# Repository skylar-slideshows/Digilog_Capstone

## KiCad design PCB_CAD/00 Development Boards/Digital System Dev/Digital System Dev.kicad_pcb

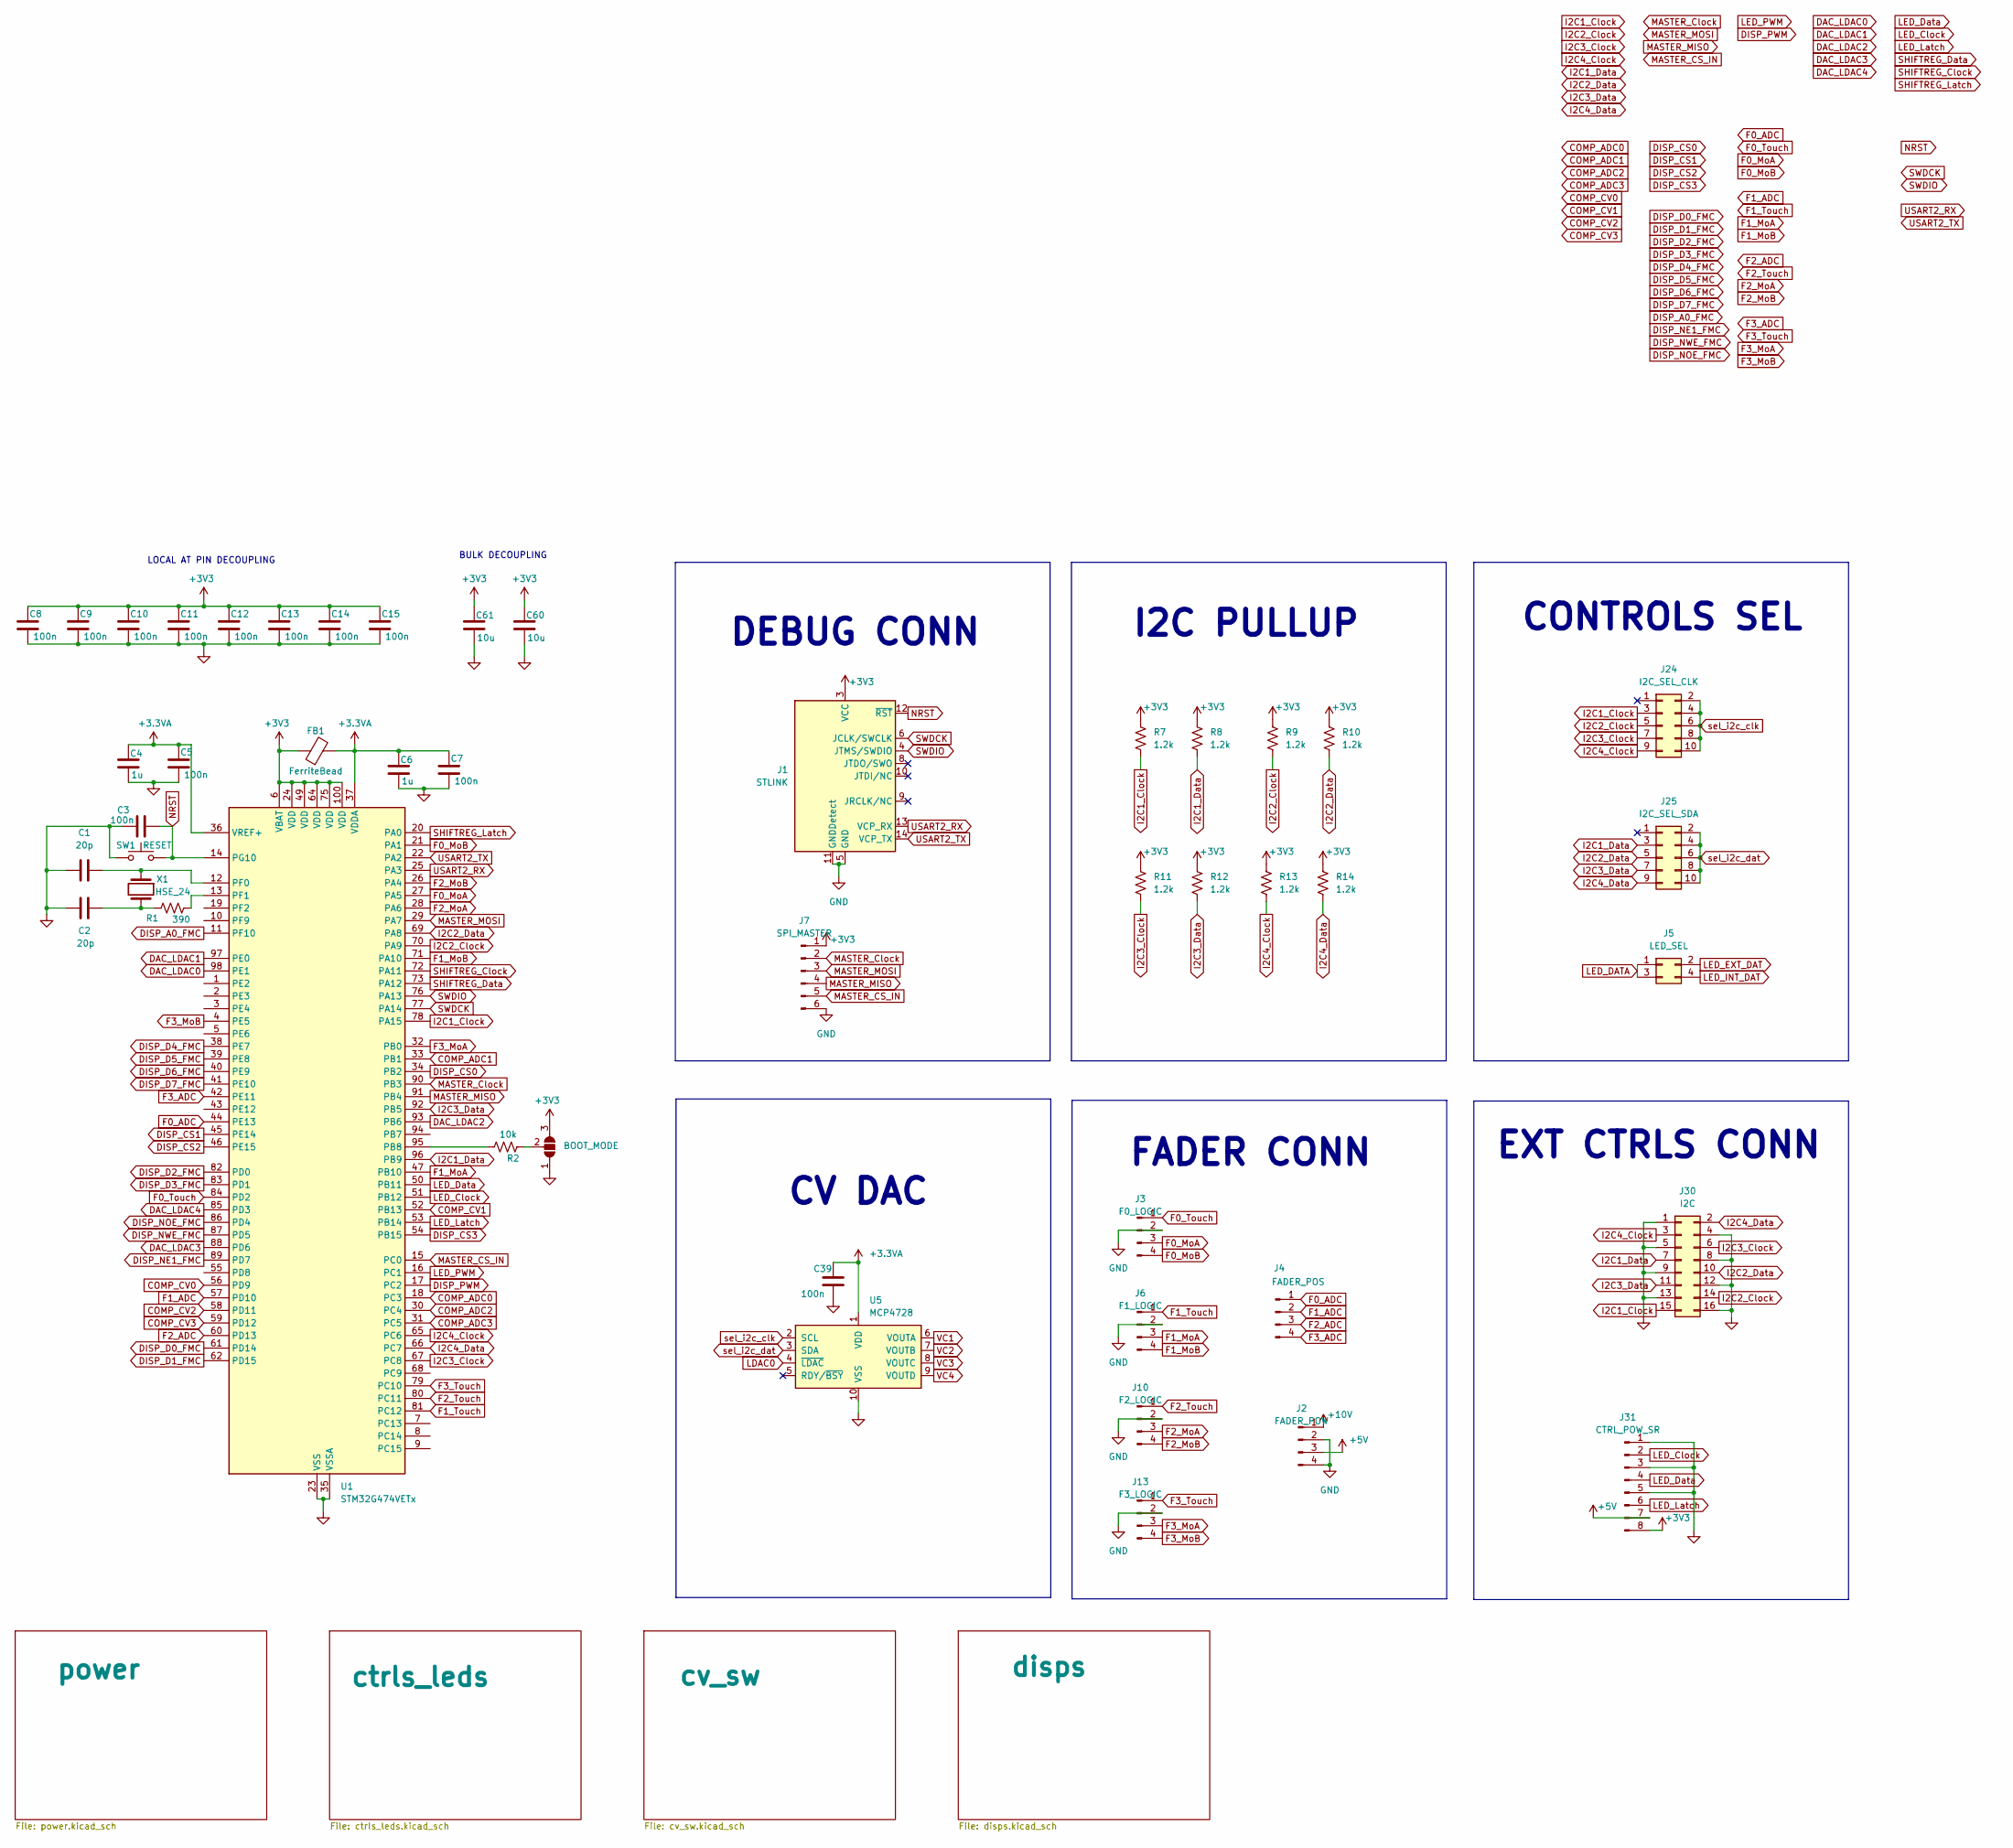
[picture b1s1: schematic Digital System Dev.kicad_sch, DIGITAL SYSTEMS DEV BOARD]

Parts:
C1, C2: 20p; C_0603_1608Metric; LCSC C1648
C3, C5, C7, C8, C9, C10, C11, C12, C13, C14, C15, C39: 100n; C_0603_1608Metric; LCSC C1590
C4, C6: 1u; C_0603_1608Metric; LCSC C1592
C60, C61: 10u; C_1206_3216Metric; LCSC C1849
FB1: FerriteBead; Ferrite_0603_1608Metric; LCSC C1002
J1: STLINK; FTSH-107-01-L-DV-K-TR; LCSC C5307809
J2: FADER_POW; PinHeader_1x04_P2.54mm_Vertical
J3: F0_LOGIC; PinHeader_1x04_P2.54mm_Vertical
J4: FADER_POS; PinHeader_1x04_P2.54mm_Vertical
J5: LED_SEL; PinHeader_2x02_P2.54mm_Vertical
J6: F1_LOGIC; PinHeader_1x04_P2.54mm_Vertical
J7: SPI_MASTER; PinHeader_1x06_P2.54mm_Vertical
J10: F2_LOGIC; PinHeader_1x04_P2.54mm_Vertical
J13: F3_LOGIC; PinHeader_1x04_P2.54mm_Vertical
J24: I2C_SEL_CLK; PinHeader_2x05_P2.54mm_Vertical
J25: I2C_SEL_SDA; PinHeader_2x05_P2.54mm_Vertical
J30: I2C; PinHeader_2x08_P1.27mm_Vertical
J31: CTRL_POW_SR; PinHeader_1x08_P2.54mm_Vertical
R1: 390; R_1206_3216Metric; LCSC C497314
R2: 10k
R7, R8, R9, R10, R11, R12, R13, R14: 1.2k
SP1: BOOT_MODE; SolderJumper-3_P2.0mm_Open_TrianglePad1.0x1.5mm
SW1: RESET; SW_Push_1P1T_NO_CK_KMR2; LCSC C72443
U1: STM32G474VETx; LQFP-100_14x14mm_P0.5mm; LCSC C2970837
U5: MCP4728; MSOP-10_3x3mm_P0.5mm; LCSC C478093
X1: HSE_24; Crystal_SMD_HC49-SD; LCSC C117881

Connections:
+3.3VA: C4.1, C5.1, C6.1, C7.1, C39.1, FB1.2, U1.36 (VREF+), U1.37 (VDDA), U5.1 (VDD)
+3V3: C8.1, C9.1, C10.1, C11.1, C12.1, C13.1, C14.1, C15.1, C60.1, C61.1, FB1.1, J1.3 (VCC), J7.1, J31.8, R7.1, R8.1, R9.1, R10.1, R11.1, R12.1, R13.1, R14.1, SP1.3 (B), U1.6 (VBAT), U1.24 (VDD), U1.49 (VDD), U1.64 (VDD), U1.75 (VDD), U1.100 (VDD); also elsewhere on the board
+5V: J2.3, J31.7; also elsewhere on the board
+10V: J2.1; also elsewhere on the board
COMP_ADC0: U1.18 (PC3)
COMP_ADC1: U1.33 (PB1)
COMP_ADC2: U1.30 (PC4)
COMP_ADC3: U1.31 (PC5)
COMP_CV0: U1.56 (PD9)
COMP_CV1: U1.52 (PB13)
COMP_CV2: U1.58 (PD11)
COMP_CV3: U1.59 (PD12)
DAC_LDAC0: U1.98 (PE1)
DAC_LDAC1: U1.97 (PE0)
DAC_LDAC2: U1.93 (PB6)
DAC_LDAC3: U1.88 (PD6)
DAC_LDAC4: U1.85 (PD3)
DISP_A0_FMC: U1.11 (PF10)
DISP_CS0: U1.34 (PB2)
DISP_CS1: U1.45 (PE14)
DISP_CS2: U1.46 (PE15)
DISP_CS3: U1.54 (PB15)
DISP_D0_FMC: U1.61 (PD14)
DISP_D1_FMC: U1.62 (PD15)
DISP_D2_FMC: U1.82 (PD0)
DISP_D3_FMC: U1.83 (PD1)
DISP_D4_FMC: U1.38 (PE7)
DISP_D5_FMC: U1.39 (PE8)
DISP_D6_FMC: U1.40 (PE9)
DISP_D7_FMC: U1.41 (PE10)
DISP_NE1_FMC: U1.89 (PD7)
DISP_NOE_FMC: U1.86 (PD4)
DISP_NWE_FMC: U1.87 (PD5)
DISP_PWM: U1.17 (PC2); also elsewhere on the board
F0_ADC: J4.1, U1.44 (PE13)
F0_MoA: J3.3, U1.27 (PA5)
F0_MoB: J3.4, U1.21 (PA1)
F0_Touch: J3.1, U1.84 (PD2)
F1_ADC: J4.2, U1.57 (PD10)
F1_MoA: J6.3, U1.47 (PB10)
F1_MoB: J6.4, U1.71 (PA10)
F1_Touch: J6.1, U1.81 (PC12)
F2_ADC: J4.3, U1.60 (PD13)
F2_MoA: J10.3, U1.28 (PA6)
F2_MoB: J10.4, U1.26 (PA4)
F2_Touch: J10.1, U1.80 (PC11)
F3_ADC: J4.4, U1.42 (PE11)
F3_MoA: J13.3, U1.32 (PB0)
F3_MoB: J13.4, U1.4 (PE5)
F3_Touch: J13.1, U1.79 (PC10)
I2C1_Clock: J24.3, J30.15, R7.2, U1.78 (PA15)
I2C1_Data: J25.3, J30.7, R8.2, U1.96 (PB9)
I2C2_Clock: J24.5, J30.14, R9.2, U1.70 (PA9)
I2C2_Data: J25.5, J30.10, R10.2, U1.69 (PA8)
I2C3_Clock: J24.7, J30.6, R11.2, U1.67 (PC8)
I2C3_Data: J25.7, J30.11, R12.2, U1.92 (PB5)
I2C4_Clock: J24.9, J30.3, R13.2, U1.65 (PC6)
I2C4_Data: J25.9, J30.2, R14.2, U1.66 (PC7)
LDAC0: U5.4 (~LDAC)
LED_Clock: J31.2, U1.51 (PB12); also elsewhere on the board
LED_DATA: J5.1, J5.3
LED_Data: J31.4, U1.50 (PB11)
LED_EXT_DAT: J5.2
LED_INT_DAT: J5.4; also elsewhere on the board
LED_Latch: J31.6, U1.53 (PB14); also elsewhere on the board
LED_PWM: U1.16 (PC1); also elsewhere on the board
MASTER_CS_IN: J7.5, U1.15 (PC0)
MASTER_Clock: J7.2, U1.90 (PB3)
MASTER_MISO: J7.4, U1.91 (PB4)
MASTER_MOSI: J7.3, U1.29 (PA7)
NRST: C3.2, J1.12 (~RST), SW1.2, U1.14 (PG10)
unnamed: C2.2, R1.1, X1.2
unnamed: R2.2, SP1.2 (C)
unnamed: R2.1, U1.95 (PB8)
unnamed: C1.1, U1.12 (PF0), X1.1
unnamed: R1.2, U1.13 (PF1)
SHIFTREG_Clock: U1.72 (PA11); also elsewhere on the board
SHIFTREG_Data: U1.73 (PA12); also elsewhere on the board
SHIFTREG_Latch: U1.20 (PA0); also elsewhere on the board
SWDCK: J1.6 (JCLK/SWCLK), U1.77 (PA14)
SWDIO: J1.4 (JTMS/SWDIO), U1.76 (PA13)
USART2_RX: J1.13 (VCP_RX), U1.25 (PA3)
USART2_TX: J1.14 (VCP_TX), U1.22 (PA2)
VC1: U5.6 (VOUTA)
VC2: U5.7 (VOUTB)
VC3: U5.8 (VOUTC)
VC4: U5.9 (VOUTD)
sel_i2c_clk: J24.2, J24.4, J24.6, J24.8, J24.10, U5.2 (SCL); also elsewhere on the board
sel_i2c_dat: J25.2, J25.4, J25.6, J25.8, J25.10, U5.3 (SDA); also elsewhere on the board

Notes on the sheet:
I2C PULLUP
BULK DECOUPLING
DEBUG CONN
CONTROLS SEL
LOCAL AT PIN DECOUPLING
EXT CTRLS CONN
FADER CONN
CV DAC

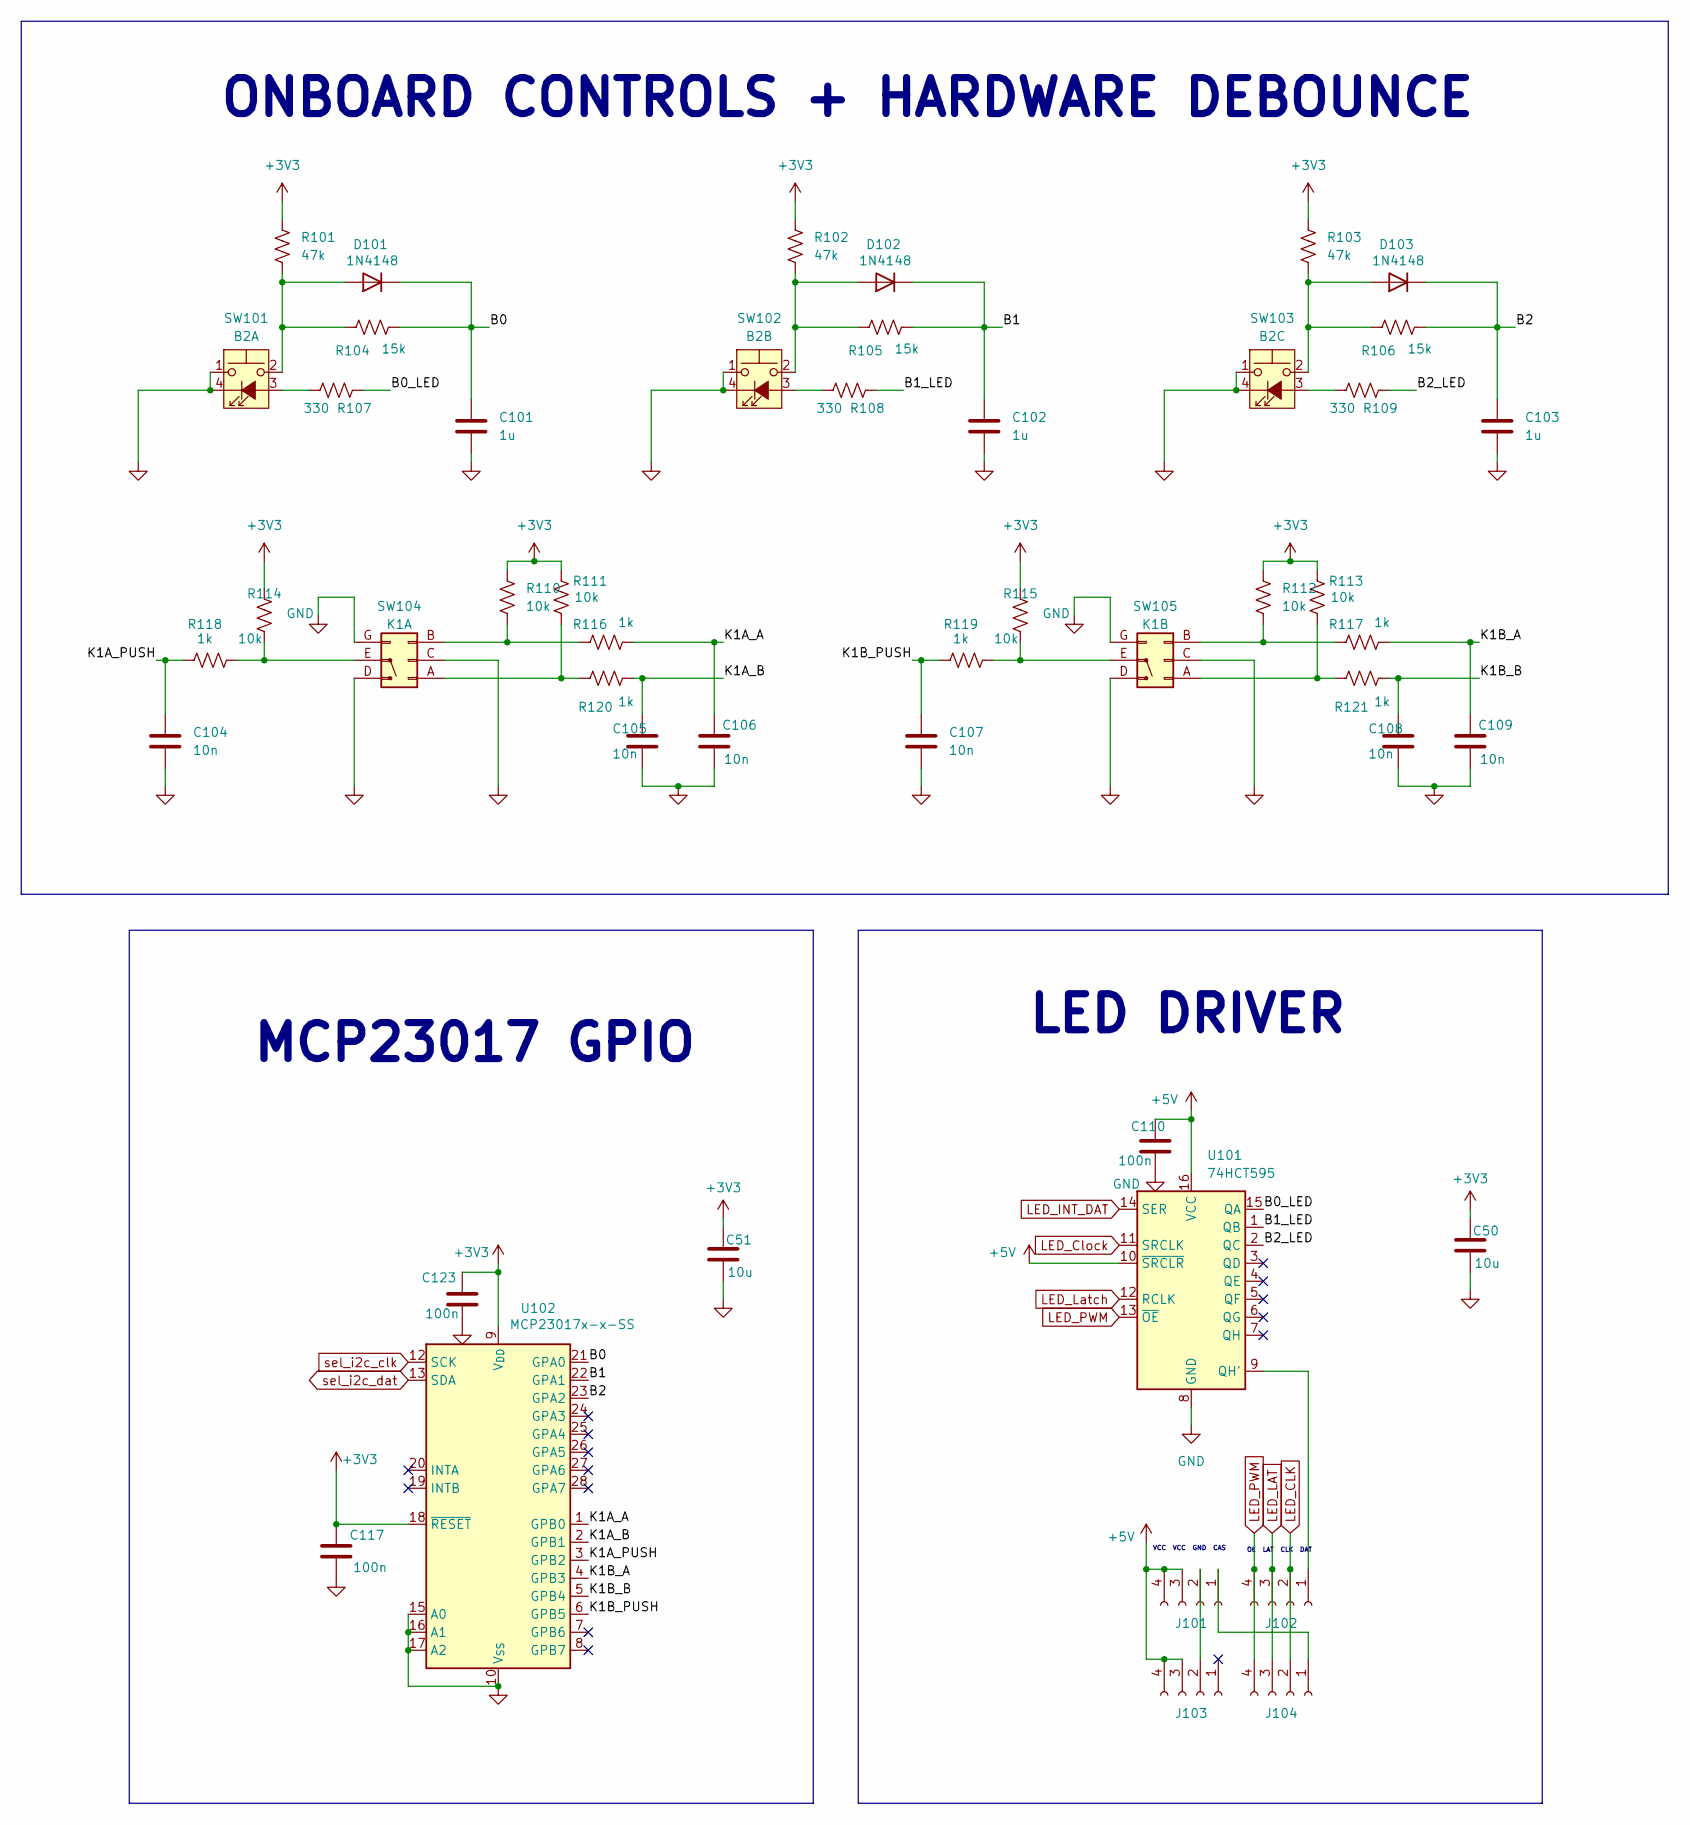
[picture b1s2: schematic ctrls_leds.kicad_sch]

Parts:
C50, C51: 10u; C_1206_3216Metric; LCSC C1849
C101, C102, C103: 1u; C_0603_1608Metric; LCSC C15849
C104, C105, C106, C107, C108, C109: 10n; C_0603_1608Metric; LCSC C57112
C110, C117, C123: 100n; C_0603_1608Metric; LCSC C1590
D101, D102, D103: 1N4148; D_SOD-323; LCSC C2128
J101, J102, J103, J104: Conn_01x04_Socket; PinSocket_1x04_P2.54mm_Vertical
R101, R102, R103: 47k; R_0603_1608Metric; LCSC C25819
R104, R105, R106: 15k; R_0603_1608Metric; LCSC C22809
R107, R108, R109: 330; R_0603_1608Metric; LCSC C23138
R110, R111, R112, R113, R114, R115: 10k; R_0603_1608Metric; LCSC C25804
R116, R117, R118, R119, R120, R121: 1k; R_0603_1608Metric; LCSC C21190
SW101: B2A; CFPB-1CC-4W6
SW102: B2B; CFPB-1CC-4W6
SW103: B2C; CFPB-1CC-4W6
SW104: K1A; EC11J0924411
SW105: K1B; EC11J0924411
U101: 74HCT595; SOIC-16_3.9x9.9mm_P1.27mm; LCSC C282339
U102: MCP23017x-x-SS; SSOP-28_5.3x10.2mm_P0.65mm

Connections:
+3V3: C50.1, C51.1, C117.1, C123.1, R101.1, R102.1, R103.1, R110.1, R111.1, R112.1, R113.1, R114.1, R115.1, U102.9 (V_{DD}), U102.18 (~RESET); also elsewhere on the board
+5V: C110.1, J101.3, J101.4, J103.3, J103.4, U101.10 (~SRCLR), U101.16 (VCC); also elsewhere on the board
/ctrls_leds/B0: C101.1, D101.1 (K), R104.2, U102.21 (GPA0)
/ctrls_leds/B0_LED: R107.2, U101.15 (QA)
/ctrls_leds/B1: C102.1, D102.1 (K), R105.2, U102.22 (GPA1)
/ctrls_leds/B1_LED: R108.2, U101.1 (QB)
/ctrls_leds/B2: C103.1, D103.1 (K), R106.2, U102.23 (GPA2)
/ctrls_leds/B2_LED: R109.2, U101.2 (QC)
/ctrls_leds/K1A_A: C106.1, R116.2, U102.1 (GPB0)
/ctrls_leds/K1A_B: C105.1, R120.2, U102.2 (GPB1)
/ctrls_leds/K1A_PUSH: C104.1, R118.1, U102.3 (GPB2)
/ctrls_leds/K1B_A: C109.1, R117.2, U102.4 (GPB3)
/ctrls_leds/K1B_B: C108.1, R121.2, U102.5 (GPB4)
/ctrls_leds/K1B_PUSH: C107.1, R119.1, U102.6 (GPB5)
LED_CLK: J102.2, J104.2
LED_Clock: U101.11 (SRCLK); also elsewhere on the board
LED_INT_DAT: U101.14 (SER); also elsewhere on the board
LED_LAT: J102.3, J104.3
LED_Latch: U101.12 (RCLK); also elsewhere on the board
LED_PWM: J102.4, J104.4, U101.13 (~OE); also elsewhere on the board
unnamed: D101.2 (A), R101.2, R104.1, SW101.2
unnamed: D102.2 (A), R102.2, R105.1, SW102.2
unnamed: D103.2 (A), R103.2, R106.1, SW103.2
unnamed: J101.1, J104.1
unnamed: J101.2, J103.2
unnamed: J102.1, U101.9 (QH')
unnamed: R107.1, SW101.3 (A)
unnamed: R108.1, SW102.3 (A)
unnamed: R109.1, SW103.3 (A)
unnamed: R111.2, R120.1, SW104.A (Pin_1)
unnamed: R110.2, R116.1, SW104.B (Pin_3)
unnamed: R114.2, R118.2, SW104.E (Pin_5)
unnamed: R113.2, R121.1, SW105.A (Pin_1)
unnamed: R112.2, R117.1, SW105.B (Pin_3)
unnamed: R115.2, R119.2, SW105.E (Pin_5)
sel_i2c_clk: U102.12 (SCK); also elsewhere on the board
sel_i2c_dat: U102.13 (SDA); also elsewhere on the board

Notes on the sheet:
OE LAT CLK DAT
MCP23017 GPIO
VCC VCC GND CAS
LED DRIVER
ONBOARD CONTROLS + HARDWARE DEBOUNCE

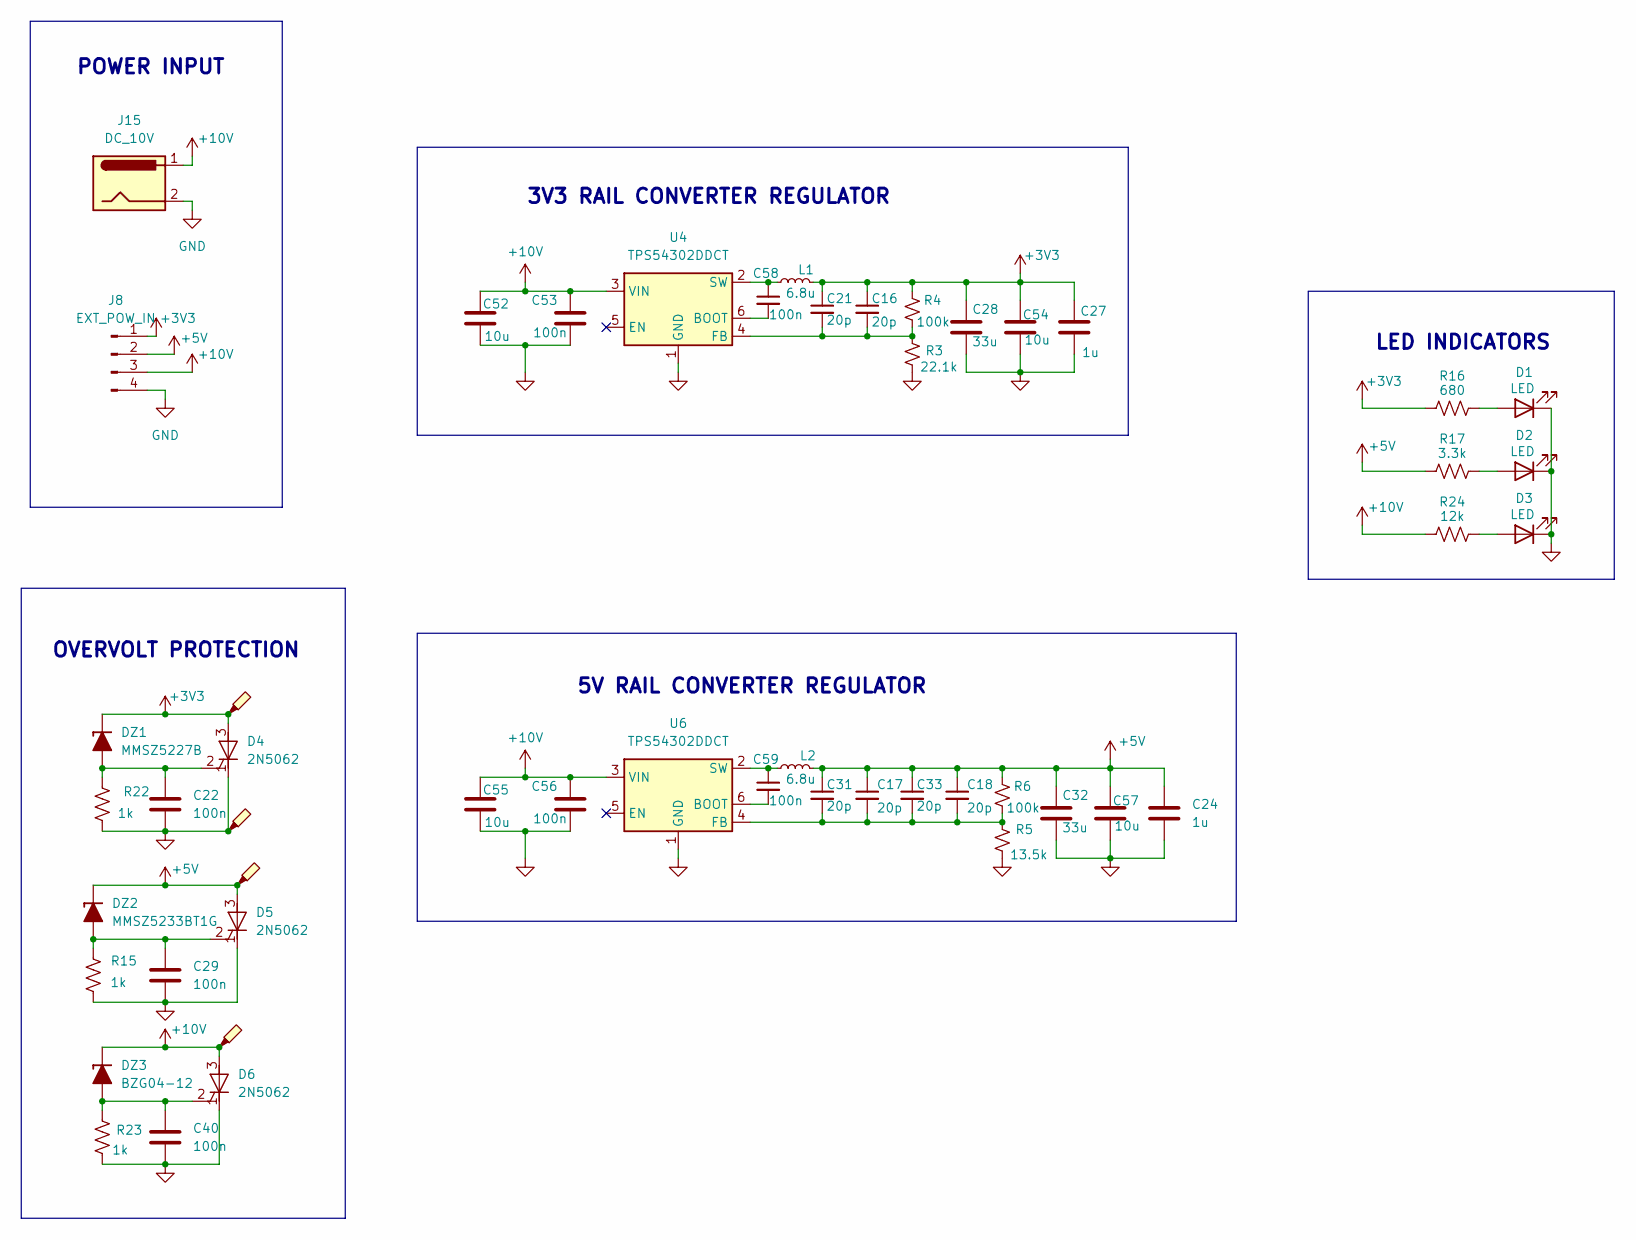
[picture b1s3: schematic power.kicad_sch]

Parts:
C16, C17, C18, C21, C31, C33: 20p; C_0603_1608Metric; LCSC C1648
C22, C29, C40, C53, C56, C58, C59: 100n; C_0603_1608Metric; LCSC C1590
C24, C27: 1u; C_0603_1608Metric; LCSC C15849
C28, C32: 33u; CP_Elec_6.3x5.4; LCSC C970684
C52, C54, C55, C57: 10u; C_1206_3216Metric; LCSC C1849
D1, D2, D3: LED; LED_0603_1608Metric; LCSC C12065
D4, D5, D6: 2N5062; TO-92
DZ1: MMSZ5227B; D_SOD-123; LCSC C707159
DZ2: MMSZ5233BT1G; D_SOD-123; LCSC C145506
DZ3: BZG04-12; D_DO-214AC_SMA; LCSC C5185905
J8: EXT_POW_IN; PinHeader_1x04_P2.54mm_Vertical
J15: DC_10V; BarrelJack_Horizontal
L1, L2: 6.8u; L_1210_3225Metric; LCSC C3040386
R3: 22.1k; R_0805_2012Metric; LCSC C17552
R4, R6: 100k
R5: 13.5k; R_0603_1608Metric; LCSC C861118
R15, R22, R23: 1k; R_0603_1608Metric; LCSC C21190
R16: 680; R_0603_1608Metric; LCSC C25822
R17: 3.3k; R_0603_1608Metric; LCSC C22978
R24: 12k; R_0603_1608Metric; LCSC C22790
TP9, TP10, TP11, TP19: TestPoint_Probe; TestPoint_Keystone_5019_Miniature
U4, U6: TPS54302DDCT; SOT-23-6; LCSC C129370

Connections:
+3V3: C16.1, C21.1, C27.1, C28.1, C54.1, D4.3 (A), DZ1.1 (K), J8.1, L1.2, R4.1, R16.1, TP9.1 (1_1); also elsewhere on the board
+5V: C17.1, C18.1, C24.1, C31.1, C32.1, C33.1, C57.1, D5.3 (A), DZ2.1 (K), J8.2, L2.2, R6.1, R17.1, TP10.1 (1_1); also elsewhere on the board
+10V: C52.1, C53.1, C55.1, C56.1, D6.3 (A), DZ3.1 (K), J8.3, J15.1, R24.1, TP11.1 (1_1), U4.3 (VIN), U6.3 (VIN); also elsewhere on the board
unnamed: D1.2 (A), R16.2
unnamed: D2.2 (A), R17.2
unnamed: D3.2 (A), R24.2
unnamed: C22.1, D4.2 (G), DZ1.2 (A), R22.2
unnamed: C29.1, D5.2 (G), DZ2.2 (A), R15.2
unnamed: C40.1, D6.2 (G), DZ3.2 (A), R23.1
unnamed 215: C16.2, C21.2, R3.1, R4.2, U4.4 (FB); also elsewhere on the board
unnamed 216: C58.1, L1.1, U4.2 (SW); also elsewhere on the board
unnamed 217: C17.2, C18.2, C31.2, C33.2, R5.1, R6.2, U6.4 (FB); also elsewhere on the board
unnamed 218: C59.1, L2.1, U6.2 (SW); also elsewhere on the board

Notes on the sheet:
LED INDICATORS
OVERVOLT PROTECTION
POWER INPUT
3V3 RAIL CONVERTER REGULATOR
5V RAIL CONVERTER REGULATOR

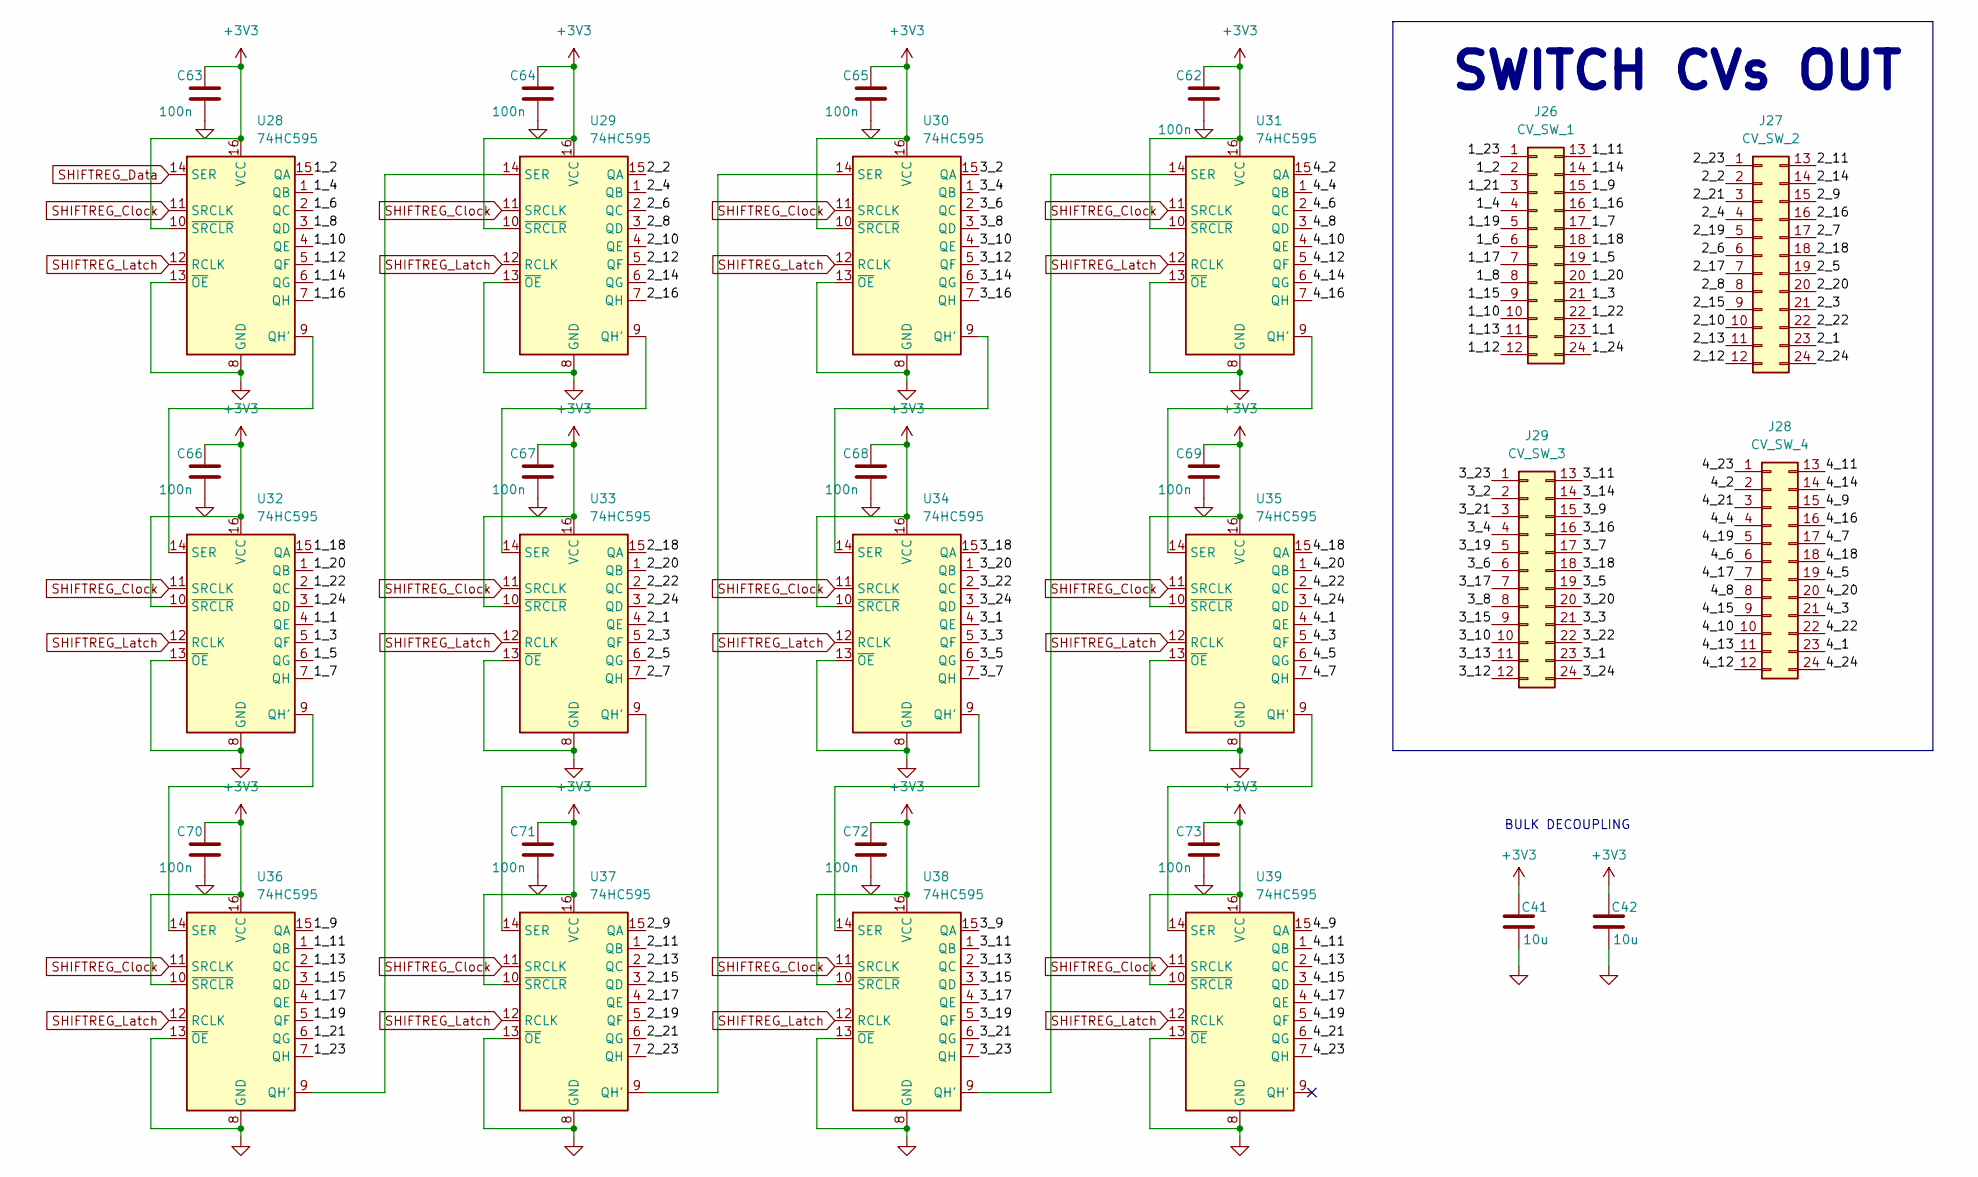
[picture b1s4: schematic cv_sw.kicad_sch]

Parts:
C41, C42: 10u; C_1206_3216Metric; LCSC C1849
C62, C63, C64, C65, C66, C67, C68, C69, C70, C71, C72, C73: 100n; C_0603_1608Metric; LCSC C1590
J26: CV_SW_1; PinHeader_2x12_P1.27mm_Vertical
J27: CV_SW_2; PinHeader_2x12_P1.27mm_Vertical
J28: CV_SW_4; PinHeader_2x12_P1.27mm_Vertical
J29: CV_SW_3; PinHeader_2x12_P1.27mm_Vertical
U28, U29, U30, U31, U32, U33, U34, U35, U36, U37, U38, U39: 74HC595; TSSOP-16_4.4x5mm_P0.65mm; LCSC C5948

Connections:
+3V3: C41.1, C42.1, C62.1, C63.1, C64.1, C65.1, C66.1, C67.1, C68.1, C69.1, C70.1, C71.1, C72.1, C73.1, U28.10 (~SRCLR), U28.16 (VCC), U29.10 (~SRCLR), U29.16 (VCC), U30.10 (~SRCLR), U30.16 (VCC), U31.10 (~SRCLR), U31.16 (VCC), U32.10 (~SRCLR), U32.16 (VCC), U33.10 (~SRCLR), U33.16 (VCC), U34.10 (~SRCLR), U34.16 (VCC), U35.10 (~SRCLR), U35.16 (VCC), U36.10 (~SRCLR), U36.16 (VCC), U37.10 (~SRCLR), U37.16 (VCC), U38.10 (~SRCLR), U38.16 (VCC), U39.10 (~SRCLR), U39.16 (VCC); also elsewhere on the board
/cv_sw/1_1: J26.23, U32.4 (QE)
/cv_sw/1_2: J26.2, U28.15 (QA)
/cv_sw/1_3: J26.21, U32.5 (QF)
/cv_sw/1_4: J26.4, U28.1 (QB)
/cv_sw/1_5: J26.19, U32.6 (QG)
/cv_sw/1_6: J26.6, U28.2 (QC)
/cv_sw/1_7: J26.17, U32.7 (QH)
/cv_sw/1_8: J26.8, U28.3 (QD)
/cv_sw/1_9: J26.15, U36.15 (QA)
/cv_sw/1_10: J26.10, U28.4 (QE)
/cv_sw/1_11: J26.13, U36.1 (QB)
/cv_sw/1_12: J26.12, U28.5 (QF)
/cv_sw/1_13: J26.11, U36.2 (QC)
/cv_sw/1_14: J26.14, U28.6 (QG)
/cv_sw/1_15: J26.9, U36.3 (QD)
/cv_sw/1_16: J26.16, U28.7 (QH)
/cv_sw/1_17: J26.7, U36.4 (QE)
/cv_sw/1_18: J26.18, U32.15 (QA)
/cv_sw/1_19: J26.5, U36.5 (QF)
/cv_sw/1_20: J26.20, U32.1 (QB)
/cv_sw/1_21: J26.3, U36.6 (QG)
/cv_sw/1_22: J26.22, U32.2 (QC)
/cv_sw/1_23: J26.1, U36.7 (QH)
/cv_sw/1_24: J26.24, U32.3 (QD)
/cv_sw/2_1: J27.23, U33.4 (QE)
/cv_sw/2_2: J27.2, U29.15 (QA)
/cv_sw/2_3: J27.21, U33.5 (QF)
/cv_sw/2_4: J27.4, U29.1 (QB)
/cv_sw/2_5: J27.19, U33.6 (QG)
/cv_sw/2_6: J27.6, U29.2 (QC)
/cv_sw/2_7: J27.17, U33.7 (QH)
/cv_sw/2_8: J27.8, U29.3 (QD)
/cv_sw/2_9: J27.15, U37.15 (QA)
/cv_sw/2_10: J27.10, U29.4 (QE)
/cv_sw/2_11: J27.13, U37.1 (QB)
/cv_sw/2_12: J27.12, U29.5 (QF)
/cv_sw/2_13: J27.11, U37.2 (QC)
/cv_sw/2_14: J27.14, U29.6 (QG)
/cv_sw/2_15: J27.9, U37.3 (QD)
/cv_sw/2_16: J27.16, U29.7 (QH)
/cv_sw/2_17: J27.7, U37.4 (QE)
/cv_sw/2_18: J27.18, U33.15 (QA)
/cv_sw/2_19: J27.5, U37.5 (QF)
/cv_sw/2_20: J27.20, U33.1 (QB)
/cv_sw/2_21: J27.3, U37.6 (QG)
/cv_sw/2_22: J27.22, U33.2 (QC)
/cv_sw/2_23: J27.1, U37.7 (QH)
/cv_sw/2_24: J27.24, U33.3 (QD)
/cv_sw/3_1: J29.23, U34.4 (QE)
/cv_sw/3_2: J29.2, U30.15 (QA)
/cv_sw/3_3: J29.21, U34.5 (QF)
/cv_sw/3_4: J29.4, U30.1 (QB)
/cv_sw/3_5: J29.19, U34.6 (QG)
/cv_sw/3_6: J29.6, U30.2 (QC)
/cv_sw/3_7: J29.17, U34.7 (QH)
/cv_sw/3_8: J29.8, U30.3 (QD)
/cv_sw/3_9: J29.15, U38.15 (QA)
/cv_sw/3_10: J29.10, U30.4 (QE)
/cv_sw/3_11: J29.13, U38.1 (QB)
/cv_sw/3_12: J29.12, U30.5 (QF)
/cv_sw/3_13: J29.11, U38.2 (QC)
/cv_sw/3_14: J29.14, U30.6 (QG)
/cv_sw/3_15: J29.9, U38.3 (QD)
/cv_sw/3_16: J29.16, U30.7 (QH)
/cv_sw/3_17: J29.7, U38.4 (QE)
/cv_sw/3_18: J29.18, U34.15 (QA)
/cv_sw/3_19: J29.5, U38.5 (QF)
/cv_sw/3_20: J29.20, U34.1 (QB)
/cv_sw/3_21: J29.3, U38.6 (QG)
/cv_sw/3_22: J29.22, U34.2 (QC)
/cv_sw/3_23: J29.1, U38.7 (QH)
/cv_sw/3_24: J29.24, U34.3 (QD)
/cv_sw/4_1: J28.23, U35.4 (QE)
/cv_sw/4_2: J28.2, U31.15 (QA)
/cv_sw/4_3: J28.21, U35.5 (QF)
/cv_sw/4_4: J28.4, U31.1 (QB)
/cv_sw/4_5: J28.19, U35.6 (QG)
/cv_sw/4_6: J28.6, U31.2 (QC)
/cv_sw/4_7: J28.17, U35.7 (QH)
/cv_sw/4_8: J28.8, U31.3 (QD)
/cv_sw/4_9: J28.15, U39.15 (QA)
/cv_sw/4_10: J28.10, U31.4 (QE)
/cv_sw/4_11: J28.13, U39.1 (QB)
/cv_sw/4_12: J28.12, U31.5 (QF)
/cv_sw/4_13: J28.11, U39.2 (QC)
/cv_sw/4_14: J28.14, U31.6 (QG)
/cv_sw/4_15: J28.9, U39.3 (QD)
/cv_sw/4_16: J28.16, U31.7 (QH)
/cv_sw/4_17: J28.7, U39.4 (QE)
/cv_sw/4_18: J28.18, U35.15 (QA)
/cv_sw/4_19: J28.5, U39.5 (QF)
/cv_sw/4_20: J28.20, U35.1 (QB)
/cv_sw/4_21: J28.3, U39.6 (QG)
/cv_sw/4_22: J28.22, U35.2 (QC)
/cv_sw/4_23: J28.1, U39.7 (QH)
/cv_sw/4_24: J28.24, U35.3 (QD)
unnamed: U28.9 (QH'), U32.14 (SER)
unnamed: U29.9 (QH'), U33.14 (SER)
unnamed: U29.14 (SER), U36.9 (QH')
unnamed: U30.9 (QH'), U34.14 (SER)
unnamed: U30.14 (SER), U37.9 (QH')
unnamed: U31.9 (QH'), U35.14 (SER)
unnamed: U31.14 (SER), U38.9 (QH')
unnamed: U32.9 (QH'), U36.14 (SER)
unnamed: U33.9 (QH'), U37.14 (SER)
unnamed: U34.9 (QH'), U38.14 (SER)
unnamed: U35.9 (QH'), U39.14 (SER)
SHIFTREG_Clock: U28.11 (SRCLK), U29.11 (SRCLK), U30.11 (SRCLK), U31.11 (SRCLK), U32.11 (SRCLK), U33.11 (SRCLK), U34.11 (SRCLK), U35.11 (SRCLK), U36.11 (SRCLK), U37.11 (SRCLK), U38.11 (SRCLK), U39.11 (SRCLK); also elsewhere on the board
SHIFTREG_Data: U28.14 (SER); also elsewhere on the board
SHIFTREG_Latch: U28.12 (RCLK), U29.12 (RCLK), U30.12 (RCLK), U31.12 (RCLK), U32.12 (RCLK), U33.12 (RCLK), U34.12 (RCLK), U35.12 (RCLK), U36.12 (RCLK), U37.12 (RCLK), U38.12 (RCLK), U39.12 (RCLK); also elsewhere on the board

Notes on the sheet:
SWITCH CVs OUT
BULK DECOUPLING

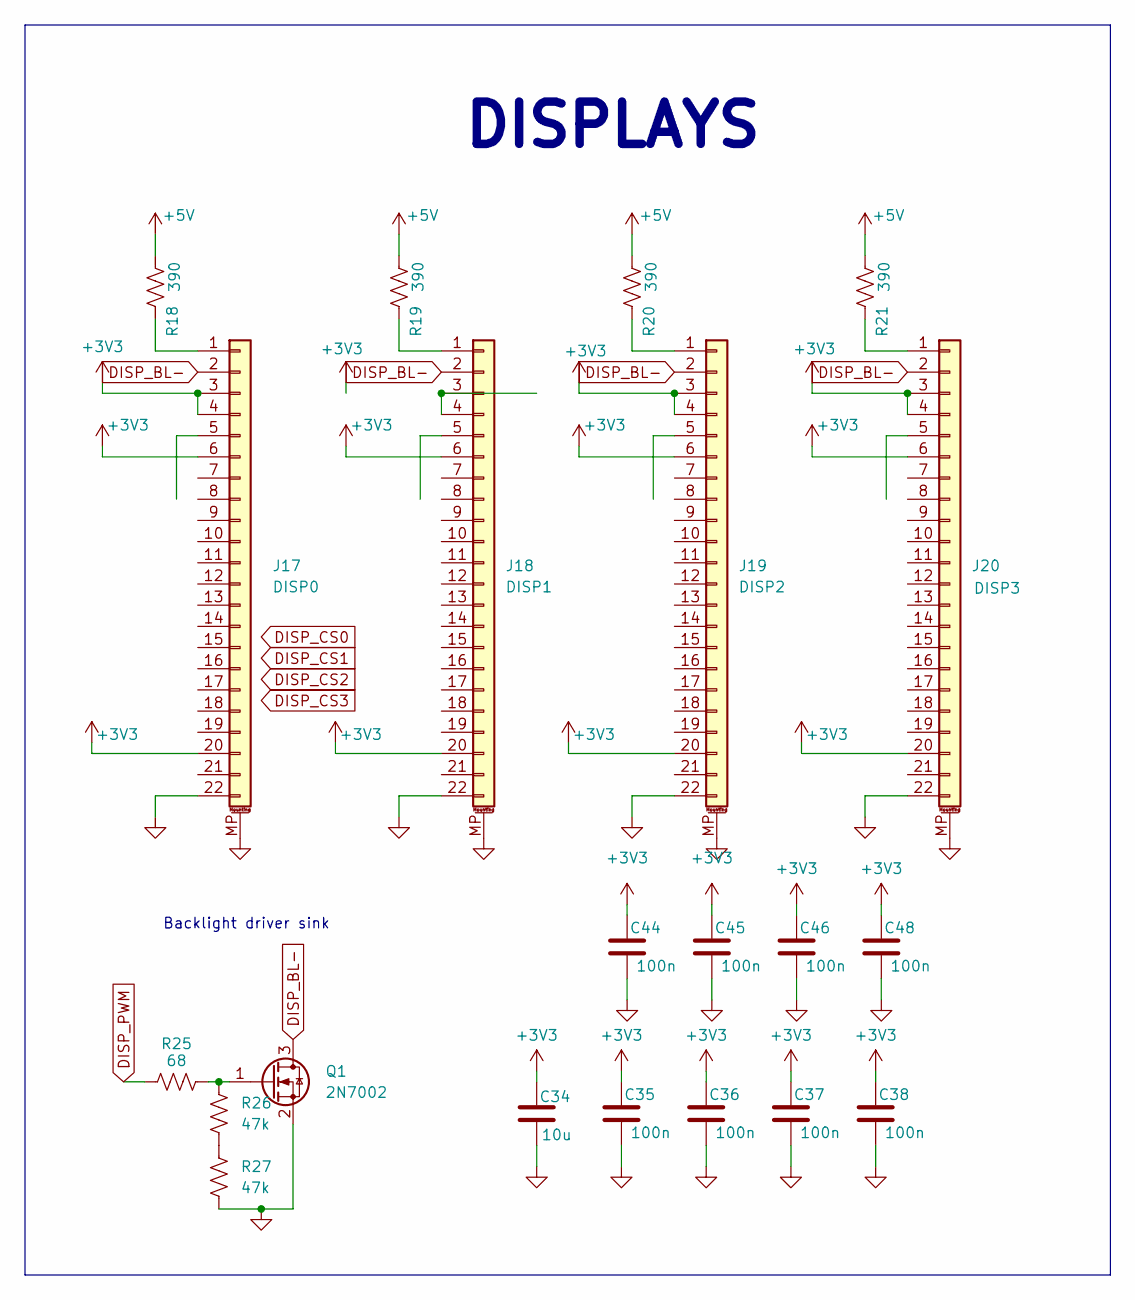
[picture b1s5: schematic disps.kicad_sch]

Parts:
C34: 10u; C_0805_2012Metric; LCSC C1713
C35, C36, C37, C38, C44, C45, C46, C48: 100n; C_0603_1608Metric; LCSC C57112
J17: DISP0; TE_2-1734839-2_1x22-1MP_P0.5mm_Horizontal; LCSC C22435644
J18: DISP1; TE_2-1734839-2_1x22-1MP_P0.5mm_Horizontal; LCSC C22435644
J19: DISP2; TE_2-1734839-2_1x22-1MP_P0.5mm_Horizontal; LCSC C22435644
J20: DISP3; TE_2-1734839-2_1x22-1MP_P0.5mm_Horizontal; LCSC C22435644
Q1: 2N7002; SOT-23; LCSC C85047
R18, R19, R20, R21: 390; R_1206_3216Metric; LCSC C497314
R25: 68; R_1206_3216Metric; LCSC C294793
R26, R27: 47k; R_0603_1608Metric; LCSC C25819

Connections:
+3V3: C34.1, C35.1, C36.1, C37.1, C38.1, C44.1, C45.1, C46.1, C48.1, J17.3, J17.4, J17.6, J17.20, J18.6, J18.20, J19.3, J19.4, J19.6, J19.20, J20.3, J20.4, J20.6, J20.20; also elsewhere on the board
+5V: R18.2, R19.2, R20.2, R21.2; also elsewhere on the board
DISP_BL-: J17.2, J18.2, J19.2, J20.2, Q1.3 (D)
DISP_PWM: R25.1; also elsewhere on the board
unnamed: J17.1, R18.1
unnamed: J18.1, R19.1
unnamed: J18.3, J18.4
unnamed: J19.1, R20.1
unnamed: J20.1, R21.1
unnamed: Q1.1 (G), R25.2, R26.1
unnamed: R26.2, R27.1

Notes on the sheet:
DISPLAYS
Backlight driver sink

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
